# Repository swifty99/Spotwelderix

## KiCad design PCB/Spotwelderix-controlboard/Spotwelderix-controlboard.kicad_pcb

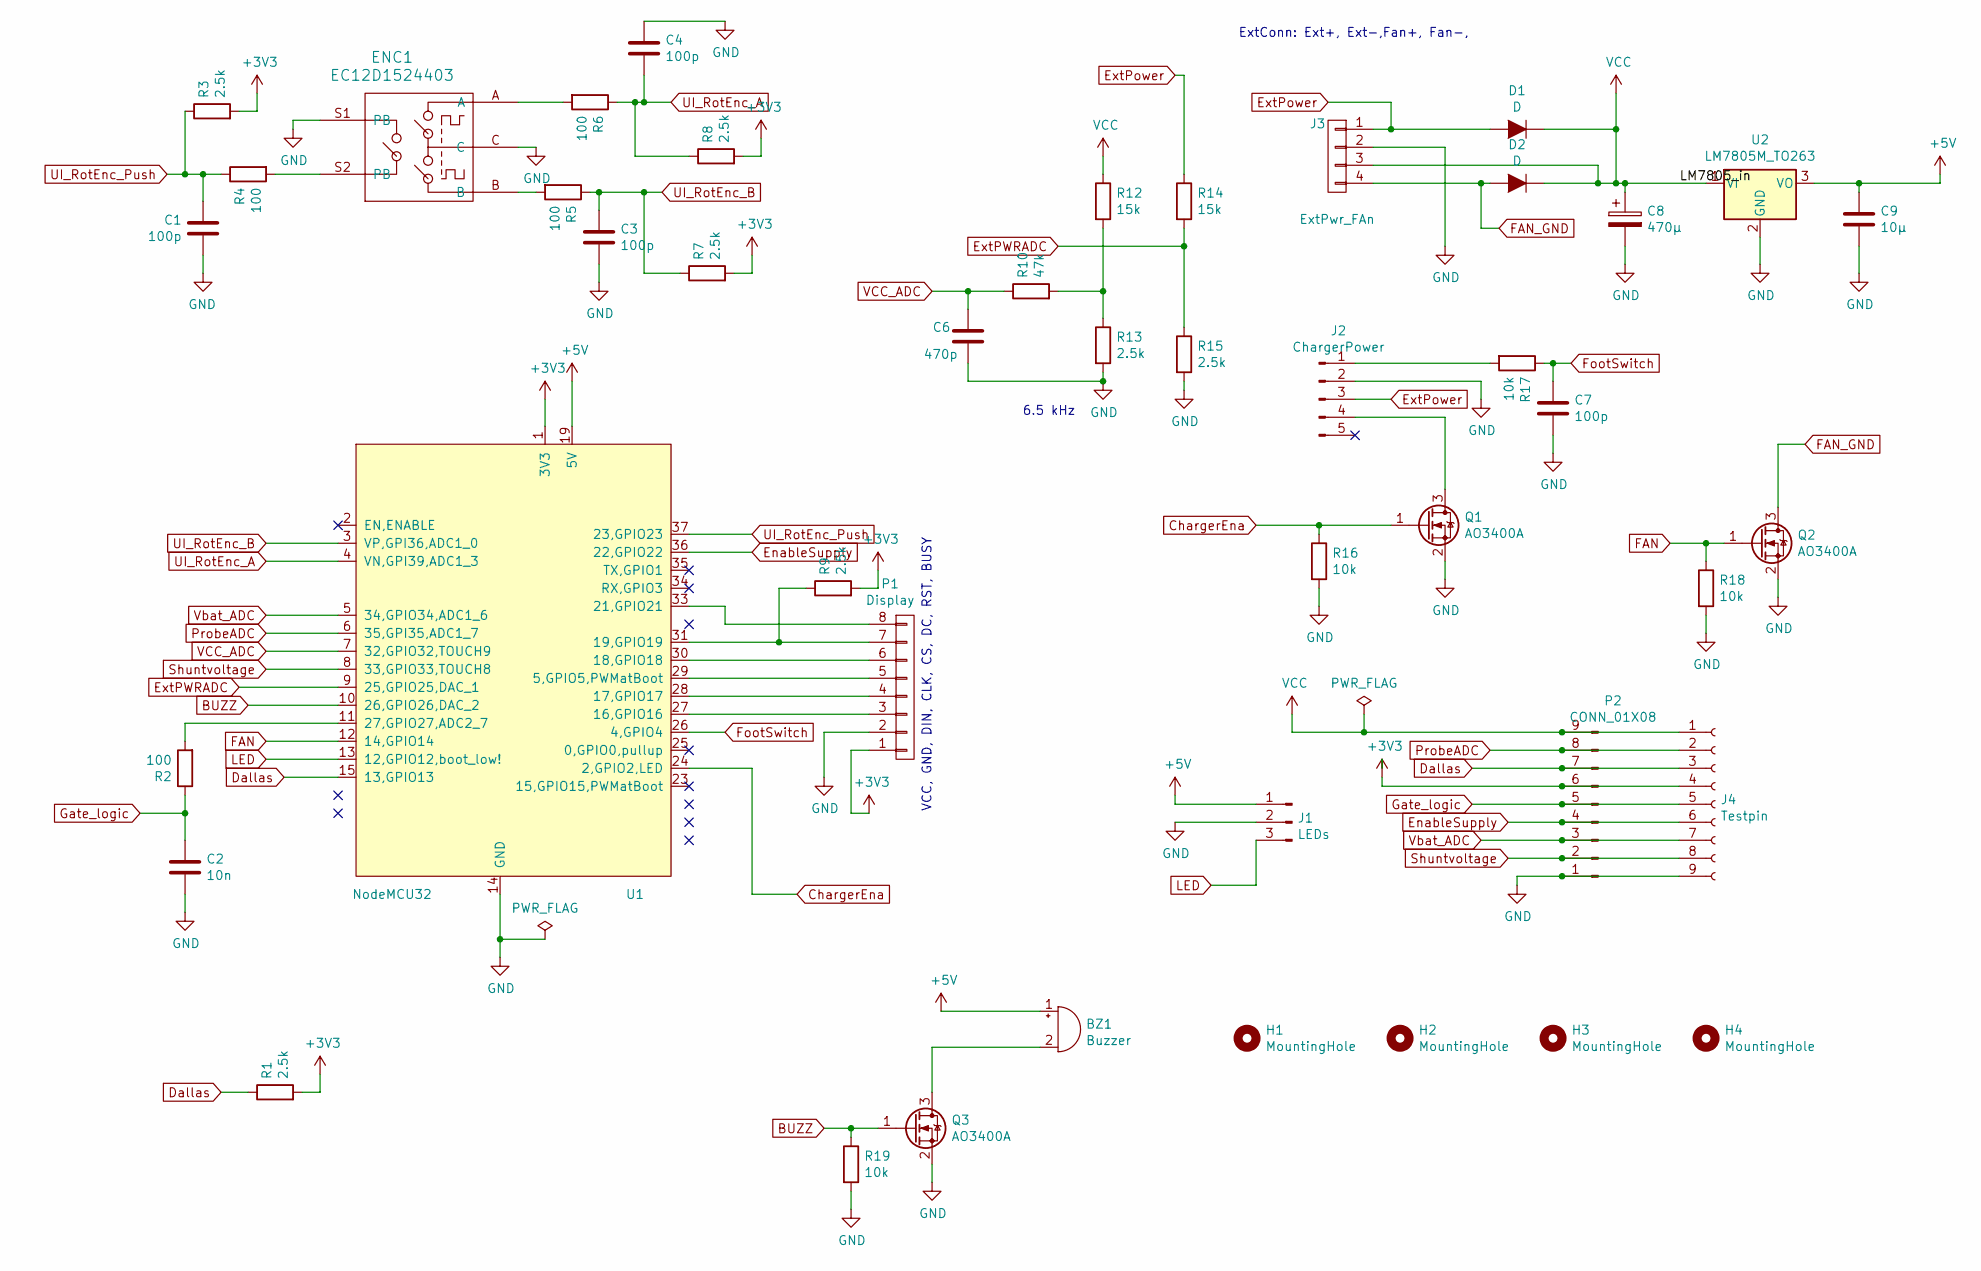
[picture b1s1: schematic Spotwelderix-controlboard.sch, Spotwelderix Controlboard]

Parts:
BZ1: Buzzer; Buzzer_15x7.5RM7.6
C1, C3, C4: 100p; C_0805_2012Metric
C2: 10n; C_1206_3216Metric_Pad1.33x1.80mm_HandSolder
C6: 470p; C_1206_3216Metric_Pad1.33x1.80mm_HandSolder
C7: 100p; C_1206_3216Metric_Pad1.33x1.80mm_HandSolder
C8: 470µ; CP_Radial_D10.0mm_P5.00mm
C9: 10µ; C_1206_3216Metric_Pad1.33x1.80mm_HandSolder
D1, D2: D; D_SMA_Handsoldering
ENC1: EC12D1524403; RotaryEncoder_Alps_EC12E-Switch_Vertical_H20mm
H1, H2, H3, H4: MountingHole; MountingHole_3.2mm_M3_DIN965_Pad_TopBottom
J1: LEDs; JST_XH_B3B-XH-A_1x03_P2.50mm_Vertical
J2: ChargerPower; JST_XH_B5B-XH-A_1x05_P2.50mm_Vertical
J3: ExtPwr_FAn; JST_XH_B4B-XH-A_1x04_P2.50mm_Vertical
J4: Testpin; PinHeader_1x09_P2.54mm_Vertical
P1: Display; JST_XH_B8B-XH-A_1x08_P2.50mm_Vertical
P2: CONN_01X08; JST_XH_B9B-XH-A_1x09_P2.50mm_Vertical
Q1, Q2, Q3: AO3400A; SOT-23
R1, R3, R7, R8, R9, R13, R15: 2.5k; R_0805_2012Metric
R2, R4, R5, R6: 100; R_0805_2012Metric
R10: 47k; R_0805_2012Metric
R12, R14: 15k; R_0805_2012Metric
R16, R17, R18, R19: 10k; R_0805_2012Metric
U1: NodeMCU32; ESP32_NODEMCU
U2: LM7805M_TO263; TO-252-2

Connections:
BUZZ: Q3.1 (G), R19.1, U1.10 (26,GPIO26,DAC_2)
ChargerEna: Q1.1 (G), R16.1, U1.24 (2,GPIO2,LED)
Dallas: J4.3, P2.7, R1.1, U1.15 (13,GPIO13)
EnableSupply: J4.6, P2.4, U1.36 (22,GPIO22)
ExtPWRADC: R14.2, R15.1, U1.9 (25,GPIO25,DAC_1)
ExtPower: D1.2 (A), J2.3, J3.1, R14.1
FAN: Q2.1 (G), R18.1, U1.12 (14,GPIO14)
FAN_GND: D2.2 (A), J3.4, Q2.3 (D)
FootSwitch: C7.1, R17.1, U1.26 (4,GPIO4)
GND: C1.2, C2.2, C3.2, C4.1, C6.2, C7.2, C8.2, C9.2, ENC1.C, ENC1.S1 (PB), J1.2, J2.2, J3.2, J4.9, P1.2, P2.1, Q1.2 (S), Q2.2 (S), Q3.2 (S), R13.2, R15.2, R16.2, R18.2, R19.2, U1.14 (GND), U1.38 (GND), U2.2 (GND)
Gate_logic: C2.1, J4.5, P2.5, R2.1
LED: J1.3, U1.13 (12,GPIO12,boot_low!)
unnamed: BZ1.2 (+), Q3.3 (D)
unnamed: ENC1.A, R6.2
unnamed: ENC1.B, R5.2
unnamed: ENC1.S2 (PB), R4.2
unnamed: J2.1, R17.2
unnamed: J2.4, Q1.3 (D)
unnamed: P1.3, U1.27 (16,GPIO16)
unnamed: P1.4, U1.28 (17,GPIO17)
unnamed: P1.5, U1.29 (5,GPIO5,PWMatBoot)
unnamed: P1.6, U1.30 (18,GPIO18)
unnamed: P1.7, R9.1, U1.31 (19,GPIO19)
unnamed: P1.8, U1.33 (21,GPIO21)
unnamed: R2.2, U1.11 (27,GPIO27,ADC2_7)
unnamed: R10.2, R12.2, R13.1
ProbeADC: J4.2, P2.8, U1.6 (35,GPI35,ADC1_7)
Probe_diff: J4.7, P2.3, U1.5 (34,GPIO34,ADC1_6); also elsewhere on the board
Shuntvoltage: J4.8, P2.2, U1.8 (33,GPIO33,TOUCH8)
UI_RotEnc_A: C4.2, R6.1, R8.1, U1.4 (VN,GPI39,ADC1_3)
UI_RotEnc_B: C3.1, R5.1, R7.1, U1.3 (VP,GPI36,ADC1_0)
UI_RotEnc_Push: C1.1, R3.1, R4.1, U1.37 (23,GPIO23)
VCC: C8.1, D1.1 (K), D2.1 (K), J3.3, J4.1, P2.9, R12.1, U2.1 (VI)
VCC_ADC: C6.1, R10.1, U1.7 (32,GPIO32,TOUCH9)

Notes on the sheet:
ExtConn: Ext+, Ext-,Fan+, Fan-,
6.5 kHz
VCC, GND, DIN, CLK, CS, DC, RST, BUSY

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
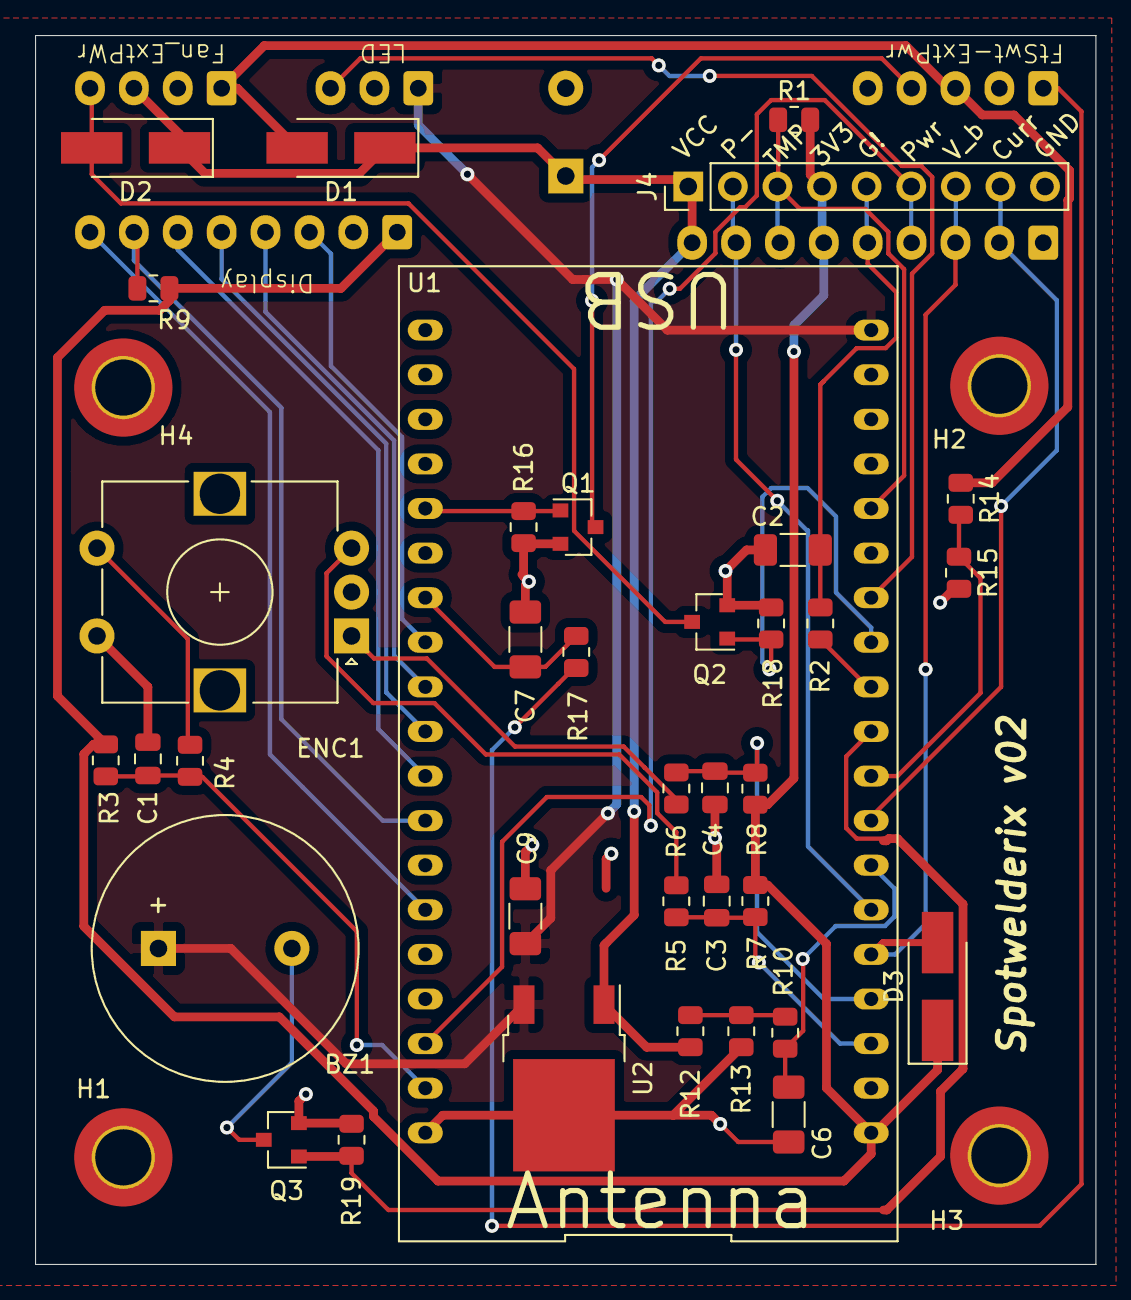
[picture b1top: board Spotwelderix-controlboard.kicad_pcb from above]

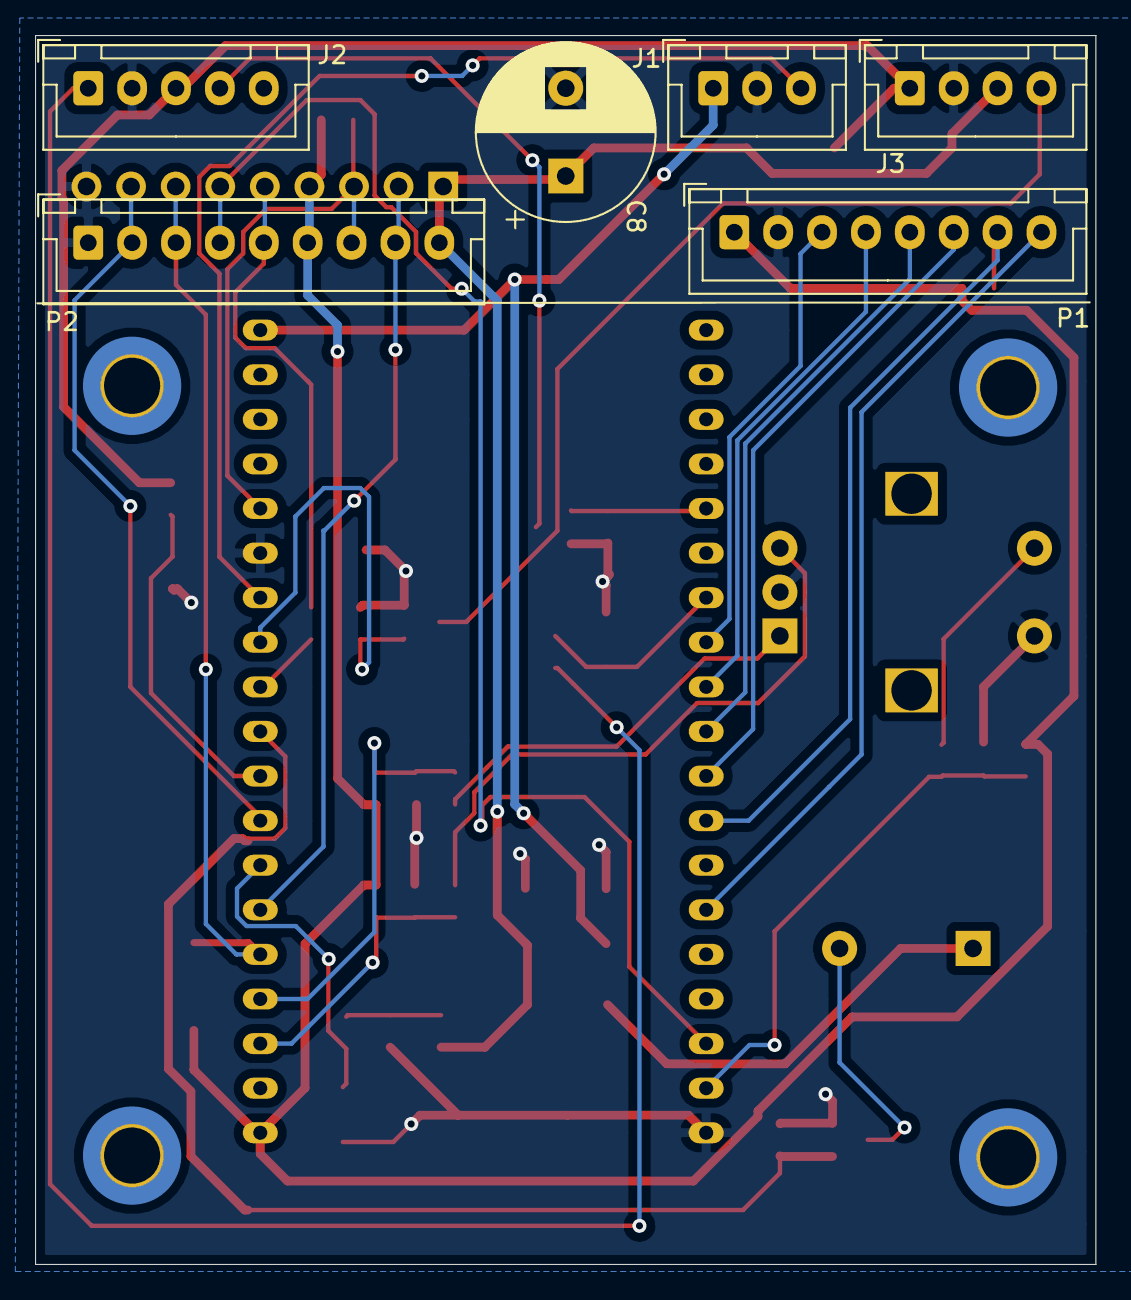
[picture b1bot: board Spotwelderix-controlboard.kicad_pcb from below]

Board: 2 copper layers, 60.4 x 70.0 mm, 46 parts (6 on the bottom side), 36 nets.

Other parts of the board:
D3: D_Schottky; D_SMA_Handsoldering

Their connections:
Probe_diff: D3.2; also elsewhere on the board

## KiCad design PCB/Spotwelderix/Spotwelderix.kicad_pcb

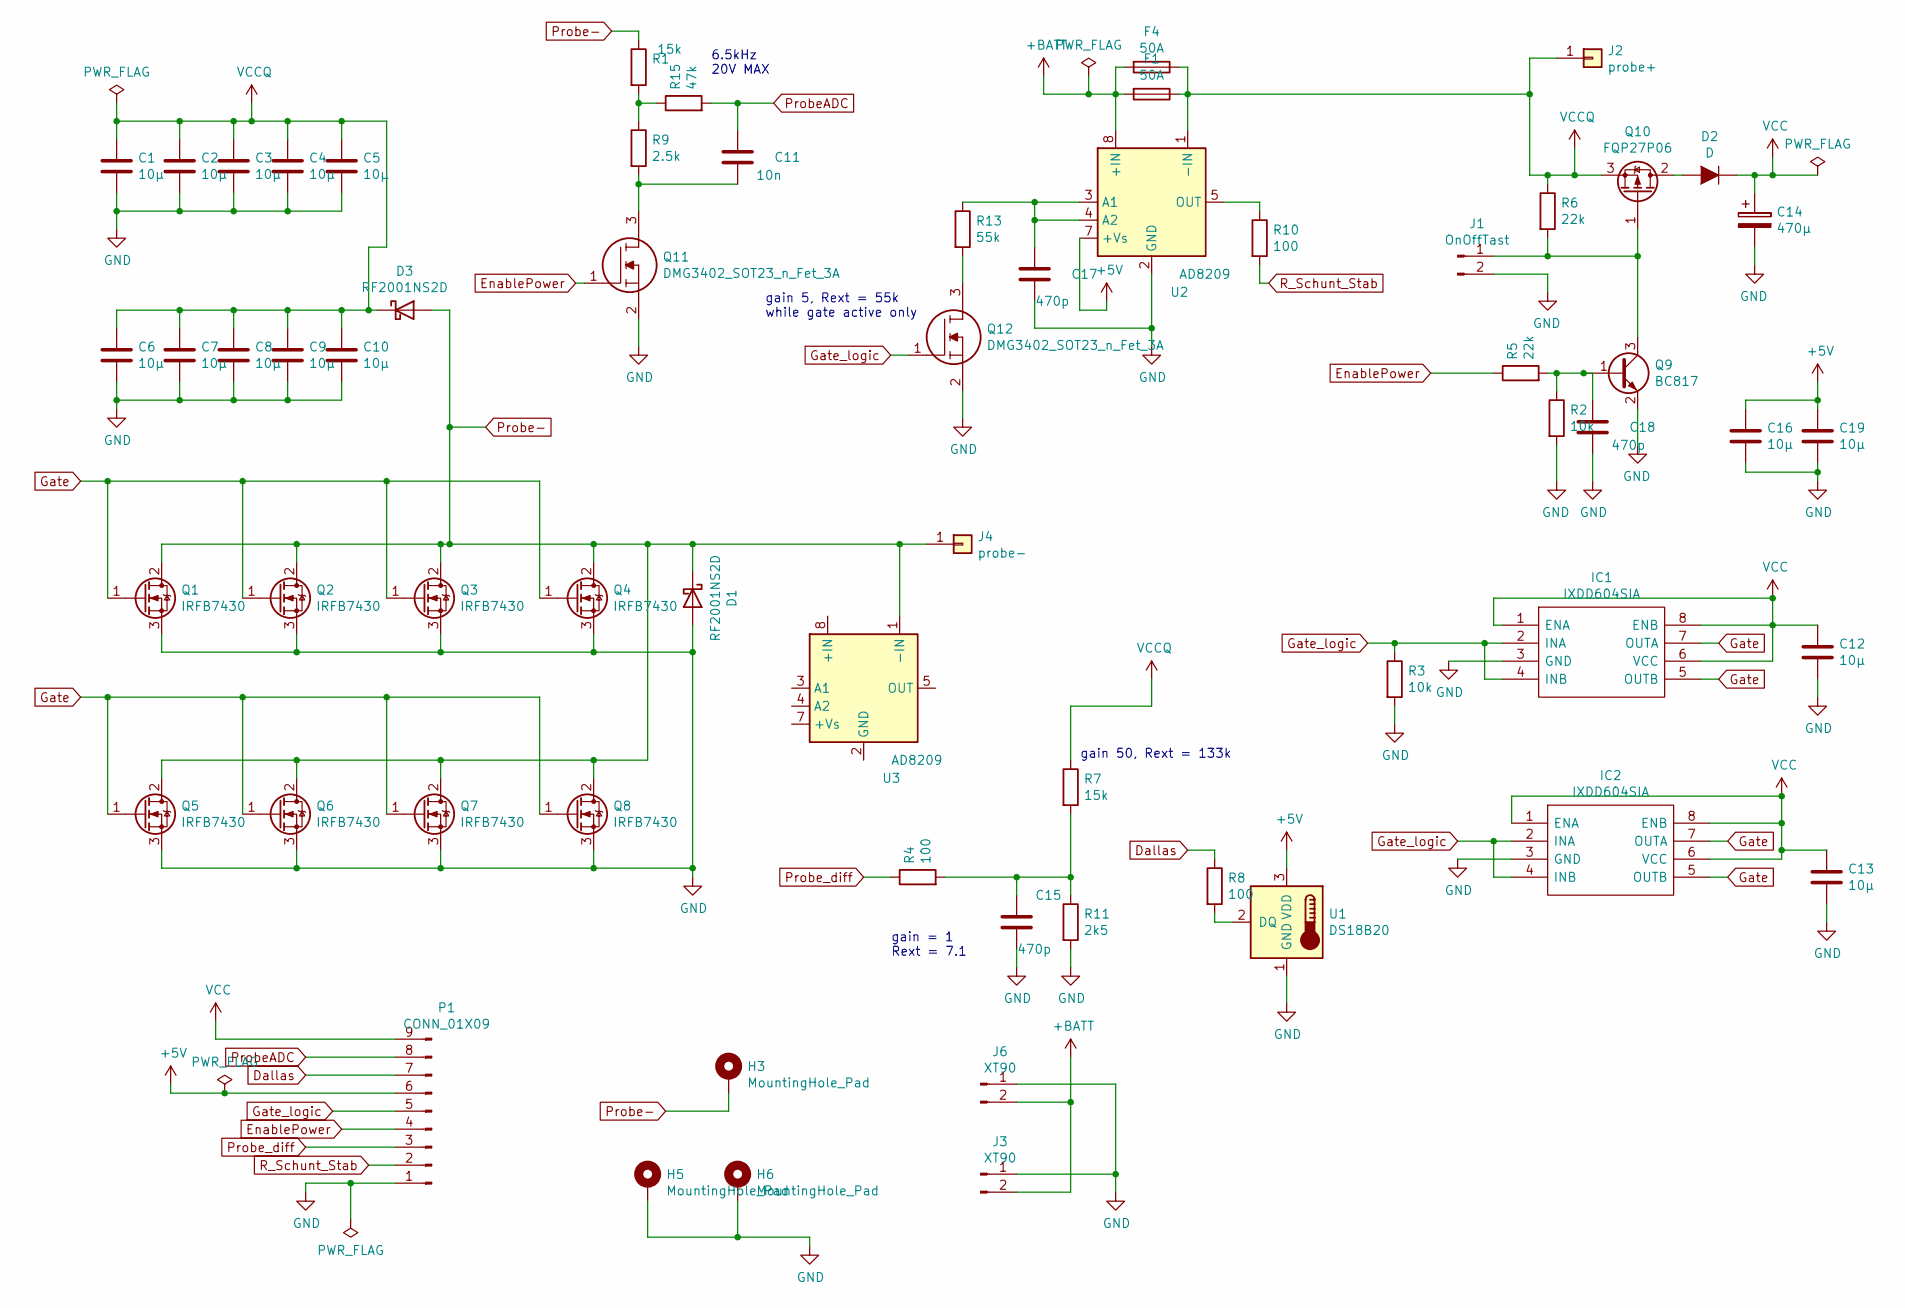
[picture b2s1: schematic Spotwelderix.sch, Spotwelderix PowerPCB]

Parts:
C1, C2, C3, C4, C5, C6, C7, C8, C9, C10, C12, C13, C16, C19: 10µ; C_1206_3216Metric
C11: 10n; C_0805_2012Metric_Pad1.18x1.45mm_HandSolder
C14: 470µ; CP_Radial_D10.0mm_P5.00mm
C15, C17, C18: 470p; C_0805_2012Metric_Pad1.18x1.45mm_HandSolder
D1, D3: RF2001NS2D; TO-263-2_TabPin1
D2: D; D_SMA_Handsoldering
F1, F4: 50A; Blade_Fuse_maxi_handsolder_1.5drill
H3, H5, H6: MountingHole_Pad; MountingHole_4.3mm_M4_Pad_Via
IC1, IC2: IXDD604SIA; SOIC127P600X175-8N; Mouser Part Number 849-IXDD604SIA
J1: OnOffTast; JST_XH_S2B-XH-A_1x02_P2.50mm_Horizontal
J2: probe+; MountingHole_5.3mm_M5_Pad_Via
J3, J6: XT90; AMASS_XT60-M_1x02_P7.20mm_Vertical
J4: probe-; MountingHole_5.3mm_M5_Pad_Via
P1: CONN_01X09; JST_XH_B9B-XH-A_1x09_P2.50mm_Vertical
Q1, Q2, Q3, Q4, Q5, Q6, Q7, Q8: IRFB7430; TO-263-2
Q9: BC817; SOT-23
Q10: FQP27P06; TO-220-3_Horizontal_TabDown
Q11, Q12: DMG3402_SOT23_n_Fet_3A; SOT-23_Handsoldering
R1, R7: 15k; R_0805_2012Metric
R2, R3: 10k; R_0805_2012Metric
R4, R8, R10: 100; R_0805_2012Metric
R5, R6: 22k; R_0805_2012Metric
R9: 2.5k; R_0805_2012Metric
R11: 2k5; R_0805_2012Metric
R13: 55k; R_0805_2012Metric
R15: 47k; R_0805_2012Metric
U1: DS18B20; TO-92_Inline_Horizontal1
U2, U3: AD8209; MSOP-8_3x3mm_P0.65mm

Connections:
+5V: C16.1, C19.1, P1.6, U1.3 (VDD), U2.7 (+Vs)
+BATT: F1.2, F4.2, J3.2, J6.2, U2.8 (+IN)
Dallas: P1.7, R8.1
EnablePower: P1.4, Q11.1, R5.1
GND: C1.2, C2.2, C3.2, C4.2, C5.2, C6.2, C7.2, C8.2, C9.2, C10.2, C12.2, C13.2, C14.2, C15.2, C16.2, C17.2, C18.2, C19.2, D1.2 (A), H5.1, H6.1, IC1.3 (GND), IC2.3 (GND), J1.2, J3.1, J6.1, P1.1, Q1.3 (S), Q2.3 (S), Q3.3 (S), Q4.3 (S), Q5.3 (S), Q6.3 (S), Q7.3 (S), Q8.3 (S), Q9.2 (E), Q11.2, Q12.2, R2.2, R3.2, R11.2, U1.1 (GND), U2.2 (GND)
Gate: IC1.5 (OUTB), IC1.7 (OUTA), IC2.5 (OUTB), IC2.7 (OUTA), Q1.1 (G), Q2.1 (G), Q3.1 (G), Q4.1 (G), Q5.1 (G), Q6.1 (G), Q7.1 (G), Q8.1 (G)
Gate_logic: IC1.2 (INA), IC1.4 (INB), IC2.2 (INA), IC2.4 (INB), P1.5, Q12.1, R3.1
unnamed: C11.2, Q11.3, R9.2
unnamed: C15.1, R4.2, R7.2, R11.1
unnamed: C17.1, R13.1, U2.3 (A1), U2.4 (A2)
unnamed: C18.1, Q9.1 (B), R2.1, R5.2
unnamed: D2.2 (A), Q10.2 (D)
unnamed: J1.1, Q9.3 (C), Q10.1 (G), R6.2
unnamed: Q12.3, R13.2
unnamed: R1.2, R9.1, R15.1
unnamed: R8.2, U1.2 (DQ)
unnamed: R10.1, U2.5 (OUT)
Probe-: D1.1 (K), D3.2 (A), H3.1, J4.1, Q1.2 (D), Q2.2 (D), Q3.2 (D), Q4.2 (D), Q5.2 (D), Q6.2 (D), Q7.2 (D), Q8.2 (D), R1.1, U3.1 (-IN)
ProbeADC: C11.1, P1.8, R15.2
Probe_diff: P1.3, R4.1
R_Schunt_Stab: P1.2, R10.2
VCC: C12.1, C13.1, C14.1, D2.1 (K), IC1.1 (ENA), IC1.6 (VCC), IC1.8 (ENB), IC2.1 (ENA), IC2.6 (VCC), IC2.8 (ENB), P1.9
VCCQ: C1.1, C2.1, C3.1, C4.1, C5.1, C6.1, C7.1, C8.1, C9.1, C10.1, D3.1 (K), F1.1, F4.1, J2.1, Q10.3 (S), R6.1, R7.1, U2.1 (-IN)

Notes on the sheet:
gain 5, Rext = 55k while gate active only
6.5kHz 20V MAX
gain 50, Rext = 133k
gain = 1 Rext = 7.1

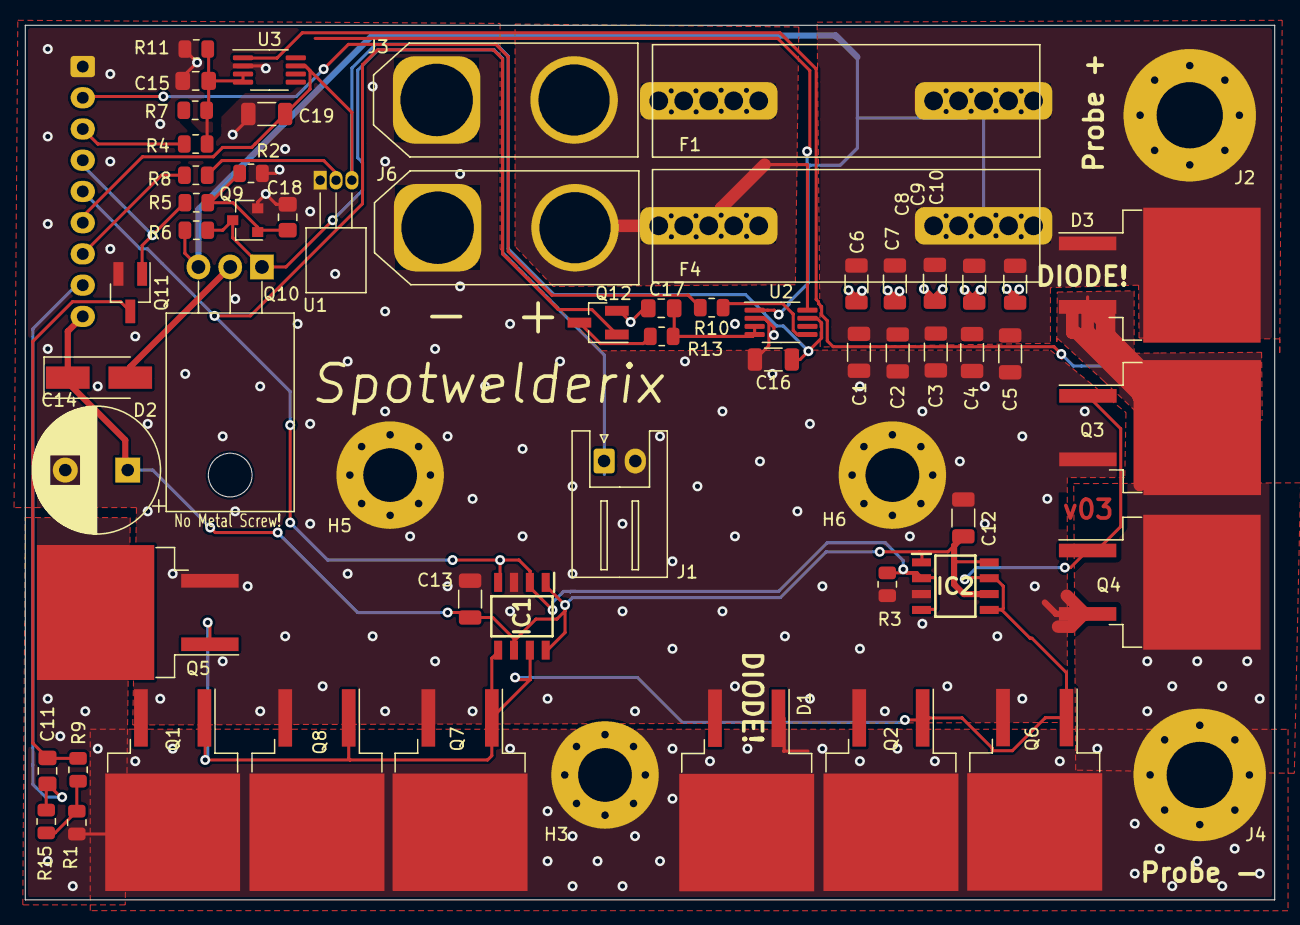
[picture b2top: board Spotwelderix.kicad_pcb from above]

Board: 2 copper layers, 100.0 x 70.0 mm, 63 parts (1 on the bottom side), 23 nets.

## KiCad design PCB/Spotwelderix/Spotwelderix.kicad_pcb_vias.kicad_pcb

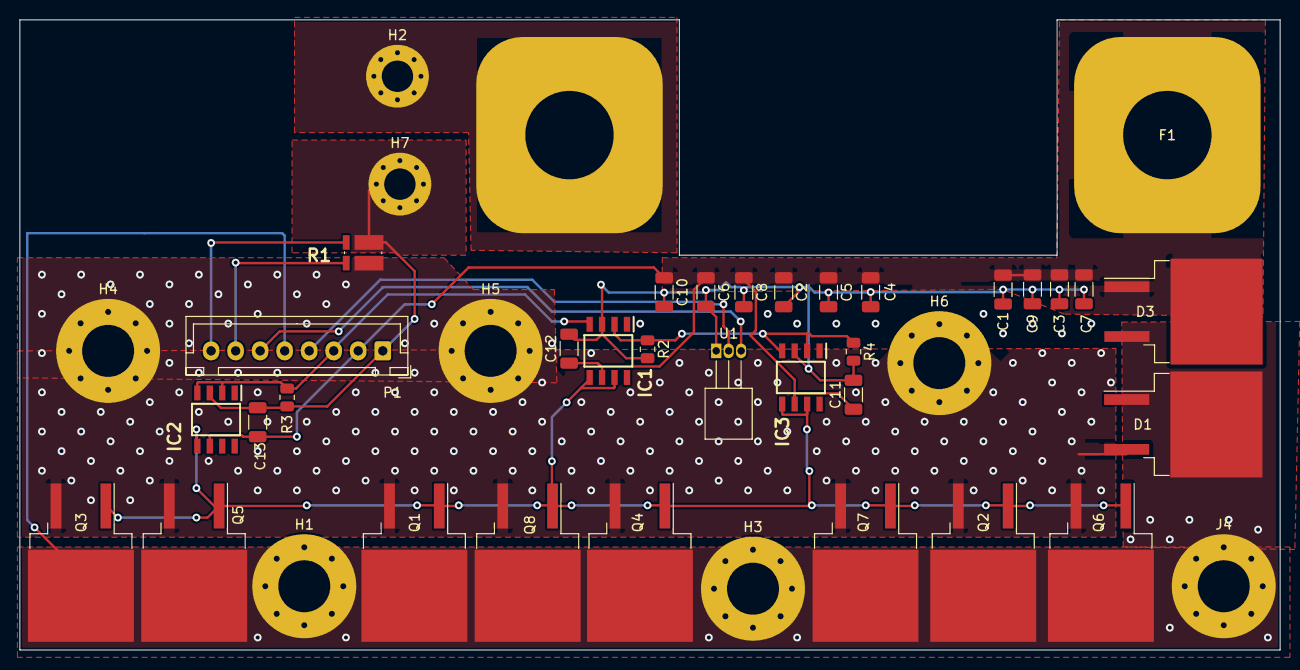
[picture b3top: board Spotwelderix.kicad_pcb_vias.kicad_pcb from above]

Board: 2 copper layers, 128.5 x 64.2 mm, 41 parts (0 on the bottom side), 11 nets.

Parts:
C1, C2, C3, C4, C5, C6, C7, C8, C9, C10, C11, C12, C13: 10µ; C_1206_3216Metric
D1, D3: RF2001NS2D; TO-263-2_TabPin1
F1: 300A; ANL_Fuse
H1, H3, H4, H5, H6: MountingHole_Pad; MountingHole_5.3mm_M5_Pad_Via
H2, H7: MountingHole_Pad; MountingHole_3.2mm_M3_Pad_Via
IC1, IC2, IC3: IXDD604SIA; SOIC127P600X175-8N
J4: probe-; MountingHole_5.3mm_M5_Pad_Via
P1: CONN_01X08; JST_XH_B8B-XH-A_1x08_P2.50mm_Vertical
Q1, Q2, Q3, Q4, Q5, Q6, Q7, Q8: IRFB7430; TO-263-2
R1: R_Shunt; WSK12161L000FEA
R2, R3, R4: 10k; R_0805_2012Metric
U1: DS18B20; TO-92_Inline_Horizontal1

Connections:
+5V: P1.6, U1.3
+BATT: F1.2, H2.1
Dallas: P1.4, U1.2
FET_GND: D1.2, H4.1, H5.1, H6.1, Q1.3, Q2.3, Q3.3, Q4.3, Q5.3, Q6.3, Q7.3, Q8.3, R1.4
GND: C1.2, C2.2, C3.2, C4.2, C5.2, C6.2, C7.2, C8.2, C9.2, C10.2, C11.2, C12.2, C13.2, H7.1, IC1.3, IC2.3, IC3.3, P1.1, R1.1, R2.2, R3.2, R4.2, U1.1
Gate: IC1.5, IC1.7, IC2.5, IC2.7, IC3.5, IC3.7, Q1.1, Q2.1, Q3.1, Q4.1, Q5.1, Q6.1, Q7.1, Q8.1
Gate_logic: IC1.2, IC1.4, IC2.2, IC2.4, IC3.2, IC3.4, P1.3, R2.1, R3.1, R4.1
Probe-: D1.1, D3.2, H1.1, H3.1, J4.1, P1.5, Q1.2, Q2.2, Q3.2, Q4.2, Q5.2, Q6.2, Q7.2, Q8.2
R_Schunt_H: P1.7, R1.3
R_Schunt_L: P1.8, R1.2
VCC: C1.1, C2.1, C3.1, C4.1, C5.1, C6.1, C7.1, C8.1, C9.1, C10.1, C11.1, C12.1, C13.1, D3.1, F1.1, IC1.6, IC2.6, IC3.6, P1.2

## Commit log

2021-01-31 power pcb added
2021-01-31 power pcb updated, added safe power for driver
2021-02-02 ena powerpcb added
2021-02-03 shunt replace
2021-02-04 ordered version v01
2021-02-05 ordered seperately
2021-08-27 pcb update 1.9
2021-08-28 windows compile
2021-08-28 same
2021-08-29 final v1
2021-08-29 PCB v2 , Power PCB routed
2021-08-29 clean up
2021-09-01 V2 tweaks and tricks
    Voltmeasure enable
2021-09-01 connector sideflip
2021-09-01 mount hole m4
2021-10-18 SW auto calibrate batt volt
2021-10-19 timing preweld done
2021-10-19 preweld 23
2022-04-01 v3 commissioning
    v3 has updated measurment devices to allow measurment of 1kA and voltages down to 0.3V accurately. Measeure the short!
2022-04-04 auto weld, non functional
2022-04-04 working display
2022-04-05 basic error message
2022-04-10 Resistance measure

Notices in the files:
PCB/Spotwelderix-controlboard/Spotwelderix-controlboard.sch:
license: https://creativecommons.org/licenses/by/4.0
